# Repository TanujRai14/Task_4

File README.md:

In this 5V power supply PCB design, I have implemented a single ground plane approach to ensure minimal noise and better return paths. 
All GND connections were routed through a dedicated polygon pour (zone) on the front layer, ensuring low impedance grounding across the board.

To connect ground pins from different locations to the main GND plane, I used vias with 0.7 mm diameter and 0.5 mm drill size, providing solid vertical connections between layers. 
The track width used throughout the layout is 0.3 mm, which is suitable for the expected current flow of up to 1–1.5 A.

The design successfully passed all Design Rule Checks (DRC), with no errors or unconnected items, confirming the integrity of the routing and electrical connectivity.

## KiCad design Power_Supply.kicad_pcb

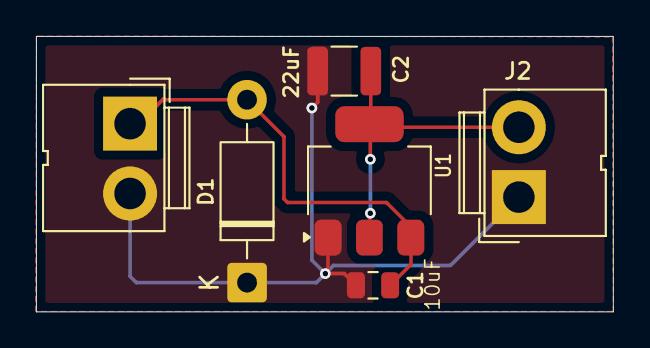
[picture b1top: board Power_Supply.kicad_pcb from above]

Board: 2 copper layers, 32.0 x 15.3 mm, 6 parts (0 on the bottom side), 3 nets.

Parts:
C1: 10uF; C_0805_2012Metric
C2: 22uF; C_1210_3225Metric
D1: 1N5819; D_DO-41_SOD81_P10.16mm_Horizontal
J1, J2: Conn_01x02_Pin; JWT_A3963_1x02_P3.96mm_Vertical
U1: AMS1117; SOT-223-3_TabPin2

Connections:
GND: C1.2, C2.2, D1.1 (K), J1.2, J2.1, U1.1 (ADJ)
unnamed: C1.1, D1.2 (A), J1.1, U1.3 (VI)
unnamed: C2.1, J2.2, U1.2 (VO)
